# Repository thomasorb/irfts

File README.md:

# irfts
Documentation on the open-IRFTS for GHG project

## stratégie d'alignement

On comencera par s'assure que le laser est bien aligné. Puis on prcédera à l'aligmenet des optiques dans cet ordre :

- séparatrice + miroir mobile

### alignement du laser

### section 1

#### sous section 1

### section 2

## chapitre 2

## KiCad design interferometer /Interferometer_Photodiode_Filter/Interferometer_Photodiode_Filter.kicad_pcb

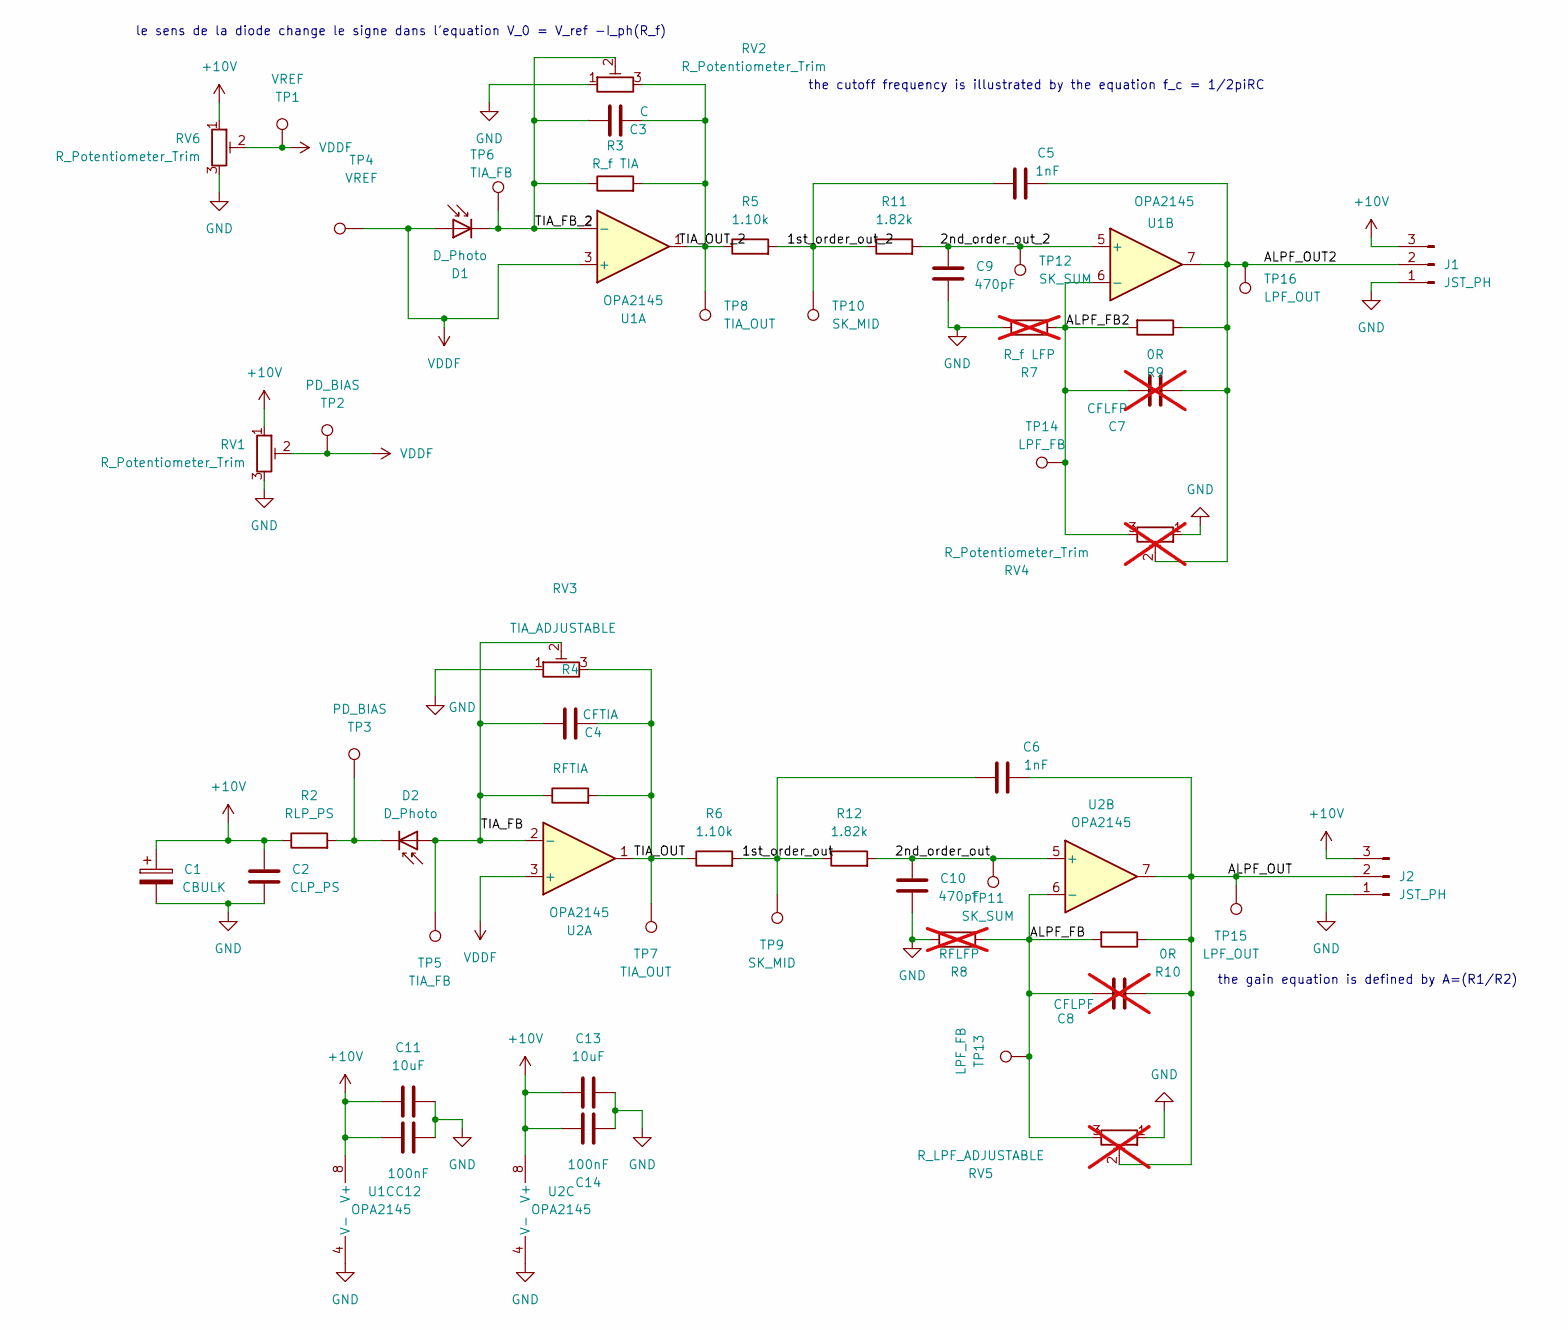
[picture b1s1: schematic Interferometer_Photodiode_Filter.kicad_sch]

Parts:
C1: CBULK; CP_EIA-7343-43_Kemet-X_HandSolder
C2: CLP_PS; C_0805_2012Metric_Pad1.18x1.45mm_HandSolder
C3: C; C_0805_2012Metric_Pad1.18x1.45mm_HandSolder
C4: CFTIA; C_0805_2012Metric_Pad1.18x1.45mm_HandSolder
C5, C6: 1nF; C_0805_2012Metric_Pad1.18x1.45mm_HandSolder
C7: CFLFP; C_0805_2012Metric_Pad1.18x1.45mm_HandSolder; not fitted
C8: CFLPF; C_0805_2012Metric_Pad1.18x1.45mm_HandSolder; not fitted
C9, C10: 470pF; C_0805_2012Metric_Pad1.18x1.45mm_HandSolder
C11, C13: 10uF; C_0805_2012Metric_Pad1.18x1.45mm_HandSolder
C12, C14: 100nF; C_0805_2012Metric_Pad1.18x1.45mm_HandSolder
D1, D2: D_Photo; SMA_Amphenol_901-144_Vertical
J1, J2: JST_PH; JST_PH_B3B-PH-SM4-TB_1x03-1MP_P2.00mm_Vertical
R2: RLP_PS; R_0805_2012Metric_Pad1.20x1.40mm_HandSolder
R3: R_f TIA; R_0805_2012Metric_Pad1.20x1.40mm_HandSolder
R4: RFTIA; R_0805_2012Metric_Pad1.20x1.40mm_HandSolder
R5, R6: 1.10k; R_0805_2012Metric_Pad1.20x1.40mm_HandSolder
R7: R_f LFP; R_0805_2012Metric_Pad1.20x1.40mm_HandSolder; not fitted
R8: RFLFP; R_0805_2012Metric_Pad1.20x1.40mm_HandSolder; not fitted
R9, R10: 0R; R_0805_2012Metric_Pad1.20x1.40mm_HandSolder
R11, R12: 1.82k; R_0805_2012Metric_Pad1.20x1.40mm_HandSolder
RV1, RV2, RV6: R_Potentiometer_Trim; Potentiometer_Bourns_3296Y_Vertical
RV3: TIA_ADJUSTABLE; Potentiometer_Bourns_3296Y_Vertical
RV4: R_Potentiometer_Trim; Potentiometer_Bourns_3296Y_Vertical; not fitted
RV5: R_LPF_ADJUSTABLE; Potentiometer_Bourns_3296Y_Vertical; not fitted
TP1, TP4: VREF; TestPoint_Pad_1.5x1.5mm
TP2, TP3: PD_BIAS; TestPoint_Pad_1.5x1.5mm
TP5, TP6: TIA_FB; TestPoint_Pad_1.5x1.5mm
TP7, TP8: TIA_OUT; TestPoint_Pad_1.5x1.5mm
TP9, TP10: SK_MID; TestPoint_Pad_1.5x1.5mm
TP11, TP12: SK_SUM; TestPoint_Pad_1.5x1.5mm
TP13, TP14: LPF_FB; TestPoint_Pad_1.5x1.5mm
TP15, TP16: LPF_OUT; TestPoint_Pad_1.5x1.5mm
U1, U2: OPA2145; SOIC-8_3.9x4.9mm_P1.27mm

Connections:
+10V: C1.1, C2.1, C11.1, C12.1, C13.1, C14.1, J1.3, J2.3, R2.1, RV1.1, RV6.1, U1.8 (V+), U2.8 (V+)
/1st_order_out: C6.1, R6.2, R12.1, TP9.1 (1_1)
/1st_order_out_2: C5.1, R5.2, R11.1, TP10.1 (1_1)
/2nd_order_out: C10.1, R12.2, TP11.1 (1_1), U2.5 (+)
/2nd_order_out_2: C9.1, R11.2, TP12.1 (1_1), U1.5 (+)
/ALPF_FB: C8.2, R8.1, R10.2, RV5.3, TP13.1 (1_1), U2.6 (-)
/ALPF_FB2: C7.2, R7.1, R9.2, RV4.3, TP14.1 (1_1), U1.6 (-)
/ALPF_OUT: C6.2, C8.1, J2.2, R10.1, RV5.2, TP15.1 (1_1), U2.7
/ALPF_OUT2: C5.2, C7.1, J1.2, R9.1, RV4.2, TP16.1 (1_1), U1.7
/TIA_FB: C4.2, D2.2 (A), R4.1, RV3.2, TP5.1 (1_1), U2.2 (-)
/TIA_FB_2: C3.2, D1.1 (K), R3.1, RV2.2, TP6.1 (1_1), U1.2 (-)
/TIA_OUT: C4.1, R4.2, R6.1, RV3.3, TP7.1 (1_1), U2.1
GND: C1.2, C2.2, C9.2, C10.2, C11.2, C12.2, C13.2, C14.2, J1.1, J2.1, R7.2, R8.2, RV1.3, RV2.1, RV3.1, RV4.1, RV5.1, RV6.3, U1.4 (V-), U2.4 (V-)
unnamed: C3.1, R3.2, R5.1, RV2.3, TP8.1 (1_1), U1.1
unnamed: D2.1 (K), R2.2, TP3.1 (1_1)
VDDF: D1.2 (A), RV1.2, RV6.2, TP1.1 (1_1), TP2.1 (1_1), TP4.1 (1_1), U1.3 (+), U2.3 (+)

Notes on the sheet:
the cutoff frequency is illustrated by the equation f_c = 1/2piRC
le sens de la diode change le signe dans l'equation V_0 = V_ref -I_ph(R_f)
the gain equation is defined by A=(R1/R2)

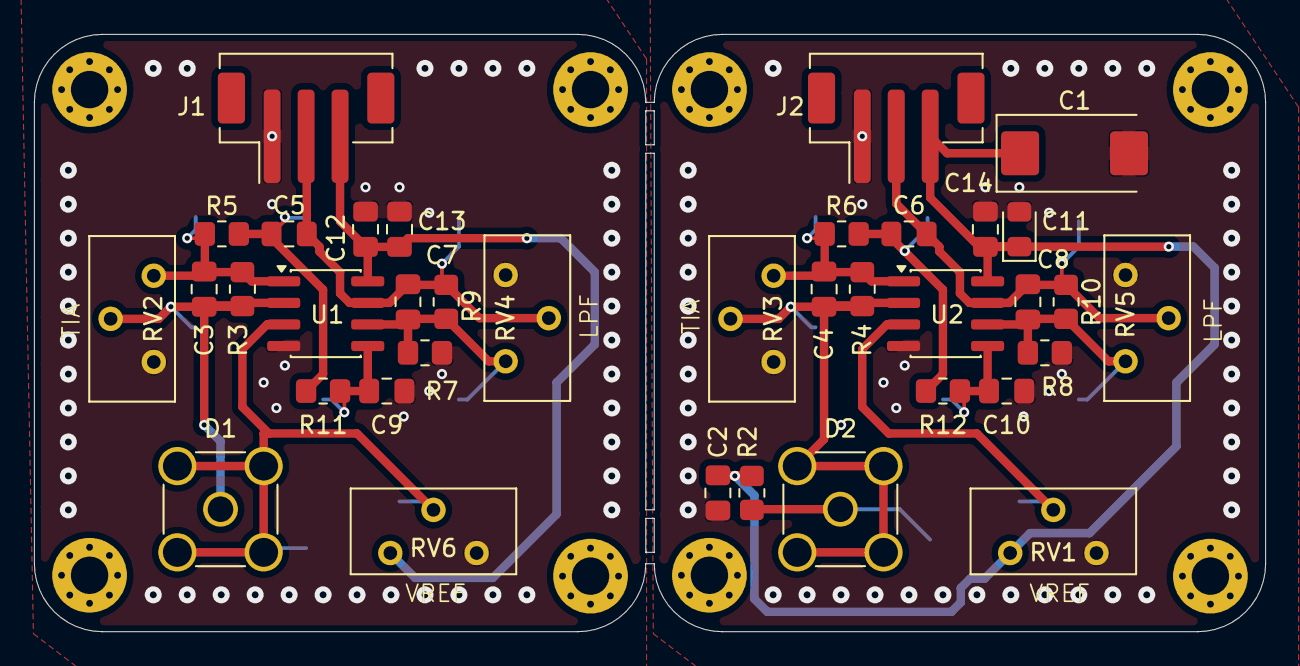
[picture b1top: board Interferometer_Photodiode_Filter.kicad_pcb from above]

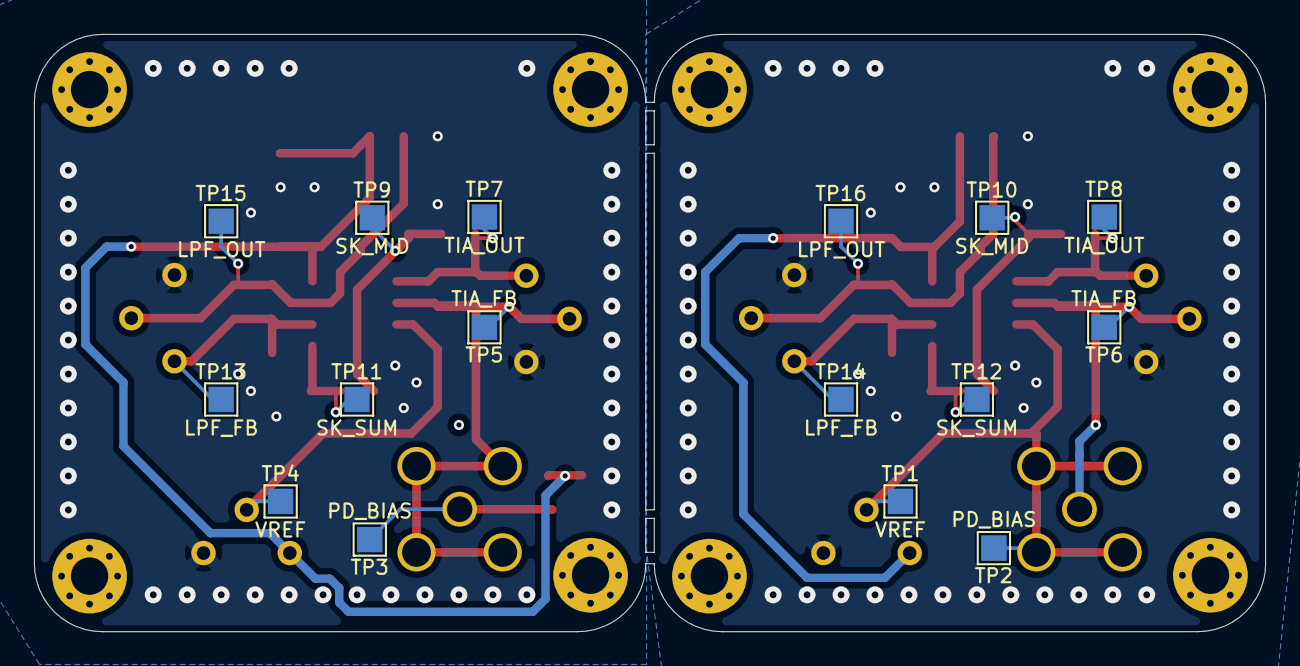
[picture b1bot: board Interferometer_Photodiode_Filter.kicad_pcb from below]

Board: 2 copper layers, 72.5 x 35.2 mm, 53 parts (16 on the bottom side), 16 nets.

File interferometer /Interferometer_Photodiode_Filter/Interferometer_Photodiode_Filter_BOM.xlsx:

DigiKey BOM
Interferometer Photodiode Filter. Butterworth build for signals through 105 kHz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
Part / value | Package | Board A refs | Board B refs | Qty A | Qty B | Total | Manufacturer | Manufacturer part number | DigiKey part number | Source
Dual JFET op amp | SOIC-8 | U1 | U2 | 1 | 1 | 2 | Texas Instruments | OPA2145IDR | 296-OPA2145IDRCT-ND | DigiKey
Vertical SMA jack | 5-pin THT | D1 | D2 | 1 | 1 | 2 | Amphenol RF | 901-144 | ARF1205-ND | DigiKey
JST PH header | 3-pin SMT, 2 mm | J1 | J2 | 1 | 1 | 2 | JST | B3B-PH-SM4-TBT | 455-B3B-PH-SM4-TBTCT-ND | DigiKey
1.10 kΩ, 1% | 0805 resistor | R5 | R6 | 1 | 1 | 2 | YAGEO | RC0805FR-071K1L | 311-1.10KCRCT-ND | DigiKey
1.82 kΩ, 1% | 0805 resistor | R11 | R12 | 1 | 1 | 2 | YAGEO | RC0805FR-071K82L | 311-1.82KCRCT-ND | DigiKey
0 Ω gain link | 0805 resistor | R9 | R10 | 1 | 1 | 2 | YAGEO | RC0805JR-070RL | 311-0.0ARCT-ND | DigiKey
1 nF, 1%, C0G, 50 V | 0805 ceramic | C5 | C6 | 1 | 1 | 2 | KEMET | C0805C102F5GACTU | 399-C0805C102F5GACTUCT-ND | DigiKey
470 pF, 1%, C0G, 50 V | 0805 ceramic | C9 | C10 | 1 | 1 | 2 | KEMET | C0805C471F5GACTU | 399-C0805C471F5GACTUCT-ND | DigiKey
10 kΩ VREF trimmer | 3296Y, THT | RV6 | RV1 | 1 | 1 | 2 | Bourns | 3296Y-1-103LF | 3296Y-103LF-ND | DigiKey
33.2 kΩ, 1% (TIA starter) | 0805 resistor | R3 | R4 | 1 | 1 | 2 | YAGEO | RC0805FR-0733K2L | 311-33.2KCRCT-ND | DigiKey
10 pF, C0G (TIA starter) | 0805 ceramic | C3 | C4 | 1 | 1 | 2 | KEMET | C0805C100J5GACTU | 399-C0805C100J5GAC7800CT-ND | DigiKey
1 kΩ, 1% (bias starter) | 0805 resistor |  | R2 | 0 | 1 | 1 | YAGEO | RC0805FR-071KL | 311-1.00KCRCT-ND | DigiKey
100 nF, X7R, 50 V | 0805 ceramic | C12 | C2, C14 | 1 | 2 | 3 | Samsung | CL21B104KBCNNNC | 1276-1003-1-ND | DigiKey
10 µF, X5R, 25 V | 0805 ceramic | C13 |  | 1 | 0 | 1 | Taiyo Yuden | TMK212BBJ106KG-T | 587-2985-1-ND | DigiKey
47 µF, tantalum, 25 V | 7343-43, X case |  | C1 | 0 | 1 | 1 | KEMET | T491X476K025AT | 399-9754-1-ND | DigiKey
 |  |  | Parts per set | 13 | 15 | 28
Assembly notes
For unity gain, fit R9/R10 as 0 Ω. Leave R7/R8, C7/C8 and RV4/RV5 unpopulated. 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
The provisional TIA build uses 33.2 kΩ and 10 pF with RV2/RV3 open. Verify gain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
C11 is marked DNP in the PCB and uses an LED-pattern footprint. C1 is the bulk 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
D1/D2 are the on-board SMA connectors. The external photodiodes, wiring and har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
TP1–TP16 are bare copper pads and require no purchased parts. The routed slots 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
For myLists, use the CSV and map DigiKey Part Number and Quantity. The JST TBT 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
